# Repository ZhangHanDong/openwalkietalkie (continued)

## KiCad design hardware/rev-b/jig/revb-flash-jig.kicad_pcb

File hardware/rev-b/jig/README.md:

# Rev B UART first-flash jig

This plate flashes a blank Rev B main board over its UART debug pads with no
soldering. The SF32's boot ROM only listens on UART1, so every new board needs
this once, for the flash table and the recovery bootloader. After that, every
update goes over USB-C (`tools/flash-usb.py`). The plate is also the way back
when a bootloader write was interrupted, and it gives you the UART debug log.

| Top (the DUT side) | Bottom |
|---|---|
|  |  |

## How it works

- The DUT lies **battery side (F) down** on the plate. The silkscreen shows its
  outline, which is mirrored because you see the board from its back.
- Three pogo pins touch the debug pads:
  - **TP6** (DUT RX)
  - **TP4** (GND)
  - **TP8** (DUT TX)

  TP3 (CAL), TP5 (reset) and TP10 (3V3) get no pin. Nothing can hold the board
  in reset or feed it through its 3.3 V rail.
- **Locators:** two M2 screws come up through the DUT's own mounting holes
  **MH2 and MH4**, so the board only fits one way.
- **Rests:** four M2×5 standoffs (REST A–D) hold the DUT's F face 5.0 mm above
  the plate.
  - The tallest F-side parts are 3.4 mm (J1/J3 PicoBlade, the USB-C shell), so
    they clear by 1.6 mm.
  - Every rest stands on bare soldermask, at least 3 mm from any F-side part or
    pad and from the board edge.
- **Hold-down:** press on the DUT's back over the pins (no parts there on the B
  side), or put a small binder clip at **CLIP**. That spot is on the DUT edge,
  over REST A.
- **Power:** plug a USB-C cable into the DUT. The plate stops at y = 3 mm, so
  the plug's overmold clears it.
- **J1** is the adapter header:

  | J1 pin | Signal | Wire to the adapter's |
  |---|---|---|
  | 1 | DUT RX | TX |
  | 2 | GND | GND |
  | 3 | DUT TX | RX |

  Any 3.3 V USB-UART adapter works; the DAPLink's CDC UART is the one used so
  far.

Every DUT position (pads, holes, outline) is read from
`../main/main-revb.kicad_pcb` by `scripts/gen_jig.py`. If the main board
moves, regenerate the plate.

## The pogo pin

**Xinyangze YZ105312061P-01, LCSC/JLCPCB C5157237** (extended part, 423 in
stock and about $0.38 on 2026-10-09).

| | |
|---|---|
| Body | 1.24 mm diameter, 0.8 mm plunger, domed tip, gold over brass |
| Length | 6.1 mm overall; operational height 4.2 mm |
| Force | 120 gf rated |
| Life | 10,000 cycles |
| Mount | Reflowed, tail in a 0.70 mm plated hole (self-centring) on a 1.5 mm ring |

Why this part:
- **Width.** TP6 and TP4 are only 2.0 mm apart. Every other pogo pin JLCPCB
  stocks is 2 mm wide (`D=2mm`), and Mill-Max's 0906 (1.07 mm plunger) is out
  of stock at JLCPCB and LCSC.
- **Force.** The 1.2–1.3 mm pins that are in stock (YZ87312060R-01,
  YZP0265-12060-01) are rated 20 gf. That is light for a jig that is pressed by
  hand.

**Check one pin with calipers when it arrives.** The datasheet has no drawing:
- The dimensions above come from the LCSC/EasyEDA 3D model and the listing.
- That model puts the free height at about **5.5 mm above the plate**, so at
  the 5.0 mm rest height the pin compresses about 0.5 mm.
- If contact is weak, use **M2×4.5** standoffs. That gives about 1.0 mm of
  compression and still stops short of the pin's ~1.5 mm stroke.
- Do not shim the standoffs up: higher rests mean less compression.

## Bill of materials

Assembled by JLCPCB (`fab-jlcpcb/`):

| Ref | Part | LCSC | Qty |
|---|---|---|---|
| P1–P3 | Pogo pin, Xinyangze YZ105312061P-01 | C5157237 | 3 |
| J1 | 1×3 2.54 mm pin header, BOOMELE | C49257 | 1 |

Hardware you add:

| Qty | Part | Where |
|---|---|---|
| 4 | M2×5 hex standoff, female–female | REST A–D |
| 4 | M2×4 screw | from below, into the rests |
| 2 | M2×10 screw | LOCATE MH2/MH4, from below |
| 2 | M2 **thin** nut (DIN 439, 1.2 mm) | on top, locks each locator screw |
| 4 | Self-adhesive bumper, about 10 mm diameter, ≥ 5 mm tall | FEET circles on the bottom |

Use the thin nut at MH4: the speaker connector J1 on the DUT hangs to 1.6 mm
above the plate beside it. A standard 1.6 mm nut would touch it. Each
locator screw ends 8.4 mm above the plate, which is 2.4 mm above the DUT's
back.

## Ordering

The JLCPCB package is in `fab-jlcpcb/`:
- `revb-flash-jig-gerber.zip`
- `revb-flash-jig-bom-jlcpcb.csv`
- `revb-flash-jig-cpl-jlcpcb.csv`

Board settings: 2 layers, 62 × 95 mm, 1.6 mm FR4. Any finish works; this is
a tool, not the DUT.

PCBA: top side only.
- The pogo pins are SMT-placed into their plated holes.
- J1 is through-hole (or solder it yourself).
- Check JLCPCB's placement preview: the pins sit 2.0 mm apart.

Order spare pins. They are rated 10k cycles.

## Using it

1. Fit the rests and locators, and stick on the feet.
2. Wire J1 to the adapter: RX→TX, TX→RX, GND.
3. Lay the DUT on the plate battery side down, with the locator screws through
   MH2/MH4. Press it down at CLIP (or clip it), and plug in USB-C.
4. Flash as for Rev A (`tools/flash-uart.py`). The port answers at any time,
   so no power-cycle timing is needed. `--compat true` (the default) covers the
   DAPLink's CDC bridge.
5. From then on, use USB-C only (`tools/flash-usb.py`).

Rev B needs the firmware pin-map changes in
[`../README.md`](../README.md#firmware-changes-needed-before-bring-up) before
its application image is usable. The flash table and bootloader do not depend
on them.

## Files

| What | Where |
|---|---|
| Board (KiCad 10.0.4, generated) | `revb-flash-jig.kicad_pcb`, `.kicad_pro` (the Rev B rules) |
| Pogo footprint + 3D model | `revb-jig.pretty/`, `models/YZ105312061P-01.wrl` (converted from the LCSC/EasyEDA model) |
| Generator | `scripts/gen_jig.py`, run with KiCad's bundled python |
| Fab outputs, DRC, renders | `scripts/make_fab.sh` → `fab-jlcpcb/`, `verification/`, `render-*.png` |
| DRC (all severities) | [`verification/revb-flash-jig-drc.rpt`](verification/revb-flash-jig-drc.rpt): 0 violations, 0 unconnected |

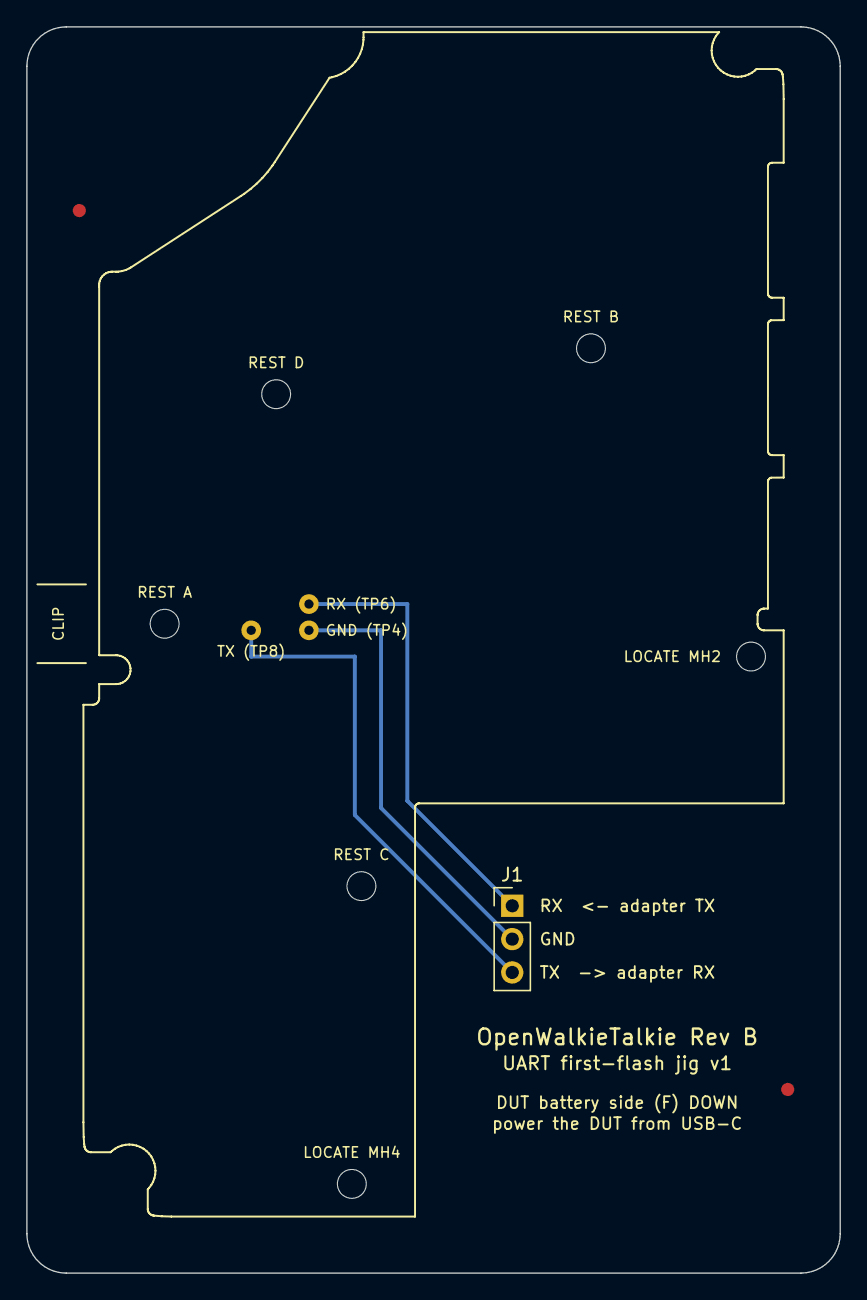
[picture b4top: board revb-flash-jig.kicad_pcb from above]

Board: 2 copper layers, 62.0 x 95.0 mm, 12 parts (0 on the bottom side), 3 nets.

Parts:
FID1, FID2: Fiducial; Fiducial_1mm_Mask2mm
H1: LOCATE MH2; MountingHole_2.2mm_M2
H2: LOCATE MH4; MountingHole_2.2mm_M2
H3: REST A; MountingHole_2.2mm_M2
H4: REST B; MountingHole_2.2mm_M2
H5: REST D; MountingHole_2.2mm_M2
H6: REST C; MountingHole_2.2mm_M2
J1: UART; PinHeader_1x03_P2.54mm_Vertical
P1, P2, P3: YZ105312061P-01; Pogo_Xinyangze_YZ105312061P-01

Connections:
DUT_RX: J1.1, P1.1
DUT_TX: J1.3, P3.1
GND: J1.2, P2.1

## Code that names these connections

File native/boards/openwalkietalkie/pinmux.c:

/*
 * SPDX-FileCopyrightText: 2019-2022 SiFli Technologies(Nanjing) Co., Ltd
 *
 * SPDX-License-Identifier: Apache-2.0
 */

#include "bsp_board.h"

#ifdef BSP_USING_PSRAM1
/* APS 128p*/
static void board_pinmux_psram_func0()
{
    HAL_PIN_Set(PAD_SA01, MPI1_DIO0, PIN_PULLDOWN, 1);
    HAL_PIN_Set(PAD_SA02, MPI1_DIO1, PIN_PULLDOWN, 1);
    HAL_PIN_Set(PAD_SA03, MPI1_DIO2, PIN_PULLDOWN, 1);
    HAL_PIN_Set(PAD_SA04, MPI1_DIO3, PIN_PULLDOWN, 1);
    HAL_PIN_Set(PAD_SA05, MPI1_DIO4, PIN_PULLDOWN, 1);
    HAL_PIN_Set(PAD_SA06, MPI1_DIO5, PIN_PULLDOWN, 1);
    HAL_PIN_Set(PAD_SA07, MPI1_DIO6, PIN_PULLDOWN, 1);
    HAL_PIN_Set(PAD_SA08, MPI1_DIO7, PIN_PULLDOWN, 1);
    HAL_PIN_Set(PAD_SA09, MPI1_DQSDM, PIN_PULLDOWN, 1);
    HAL_PIN_Set(PAD_SA10, MPI1_CLK,  PIN_NOPULL, 1);
    HAL_PIN_Set(PAD_SA11, MPI1_CS,   PIN_NOPULL, 1);

    HAL_PIN_Set_Analog(PAD_SA00, 1);
    HAL_PIN_Set_Analog(PAD_SA12, 1);
}

/* APS 1:64p 2:32P, 4:Winbond 32/64/128p*/
static void board_pinmux_psram_func1_2_4(int func)
{
    HAL_PIN_Set(PAD_SA01, MPI1_DIO0, PIN_PULLDOWN, 1);
    HAL_PIN_Set(PAD_SA02, MPI1_DIO1, PIN_PULLDOWN, 1);
    HAL_PIN_Set(PAD_SA03, MPI1_DIO2, PIN_PULLDOWN, 1);
    HAL_PIN_Set(PAD_SA04, MPI1_DIO3, PIN_PULLDOWN, 1);
    HAL_PIN_Set(PAD_SA08, MPI1_DIO4, PIN_PULLDOWN, 1);
    HAL_PIN_Set(PAD_SA09, MPI1_DIO5, PIN_PULLDOWN, 1);
    HAL_PIN_Set(PAD_SA10, MPI1_DIO6, PIN_PULLDOWN, 1);
    HAL_PIN_Set(PAD_SA11, MPI1_DIO7, PIN_PULLDOWN, 1);
    HAL_PIN_Set(PAD_SA07, MPI1_CLK,  PIN_NOPULL, 1);
    HAL_PIN_Set(PAD_SA05, MPI1_CS,   PIN_NOPULL, 1);

#ifdef FPGA
    HAL_PIN_Set(PAD_SA00, MPI1_DM, PIN_PULLDOWN, 1);
    HAL_PIN_Set(PAD_SA06, MPI1_CLKB, PIN_NOPULL, 1);
    HAL_PIN_Set(PAD_SA12, MPI1_DQSDM, PIN_PULLDOWN, 1);
#else
    switch (func)
    {
    case 1:             // APS 64P XCELLA
        HAL_PIN_Set(PAD_SA12, MPI1_DQSDM, PIN_PULLDOWN, 1);
        HAL_PIN_Set_Analog(PAD_SA00, 1);
        HAL_PIN_Set_Analog(PAD_SA06, 1);
        break;
    case 2:             // APS 32P LEGACY
        HAL_PIN_Set(PAD_SA00, MPI1_DM, PIN_PULLDOWN, 1);
        HAL_PIN_Set(PAD_SA12, MPI1_DQS, PIN_PULLDOWN, 1);
        HAL_PIN_Set(PAD_SA06, MPI1_CLKB, PIN_NOPULL, 1);
        break;
    case 4:             // Winbond 32/64/128p
        //HAL_PIN_Set(PAD_SA06, MPI1_CLKB, PIN_NOPULL, 1);
        HAL_PIN_Set(PAD_SA12, MPI1_DQSDM, PIN_NOPULL, 1);
        HAL_PIN_Set_Analog(PAD_SA00, 1);
        HAL_PIN_Set_Analog(PAD_SA06, 1);
        break;
    }
#endif
}

/* APS 16p*/
static void board_pinmux_psram_func3()
{
    HAL_PIN_Set(PAD_SA09, MPI1_CLK, PIN_NOPULL, 1);
    HAL_PIN_Set(PAD_SA08, MPI1_CS,  PIN_NOPULL, 1);
    HAL_PIN_Set(PAD_SA05, MPI1_DIO0, PIN_PULLDOWN, 1);
    HAL_PIN_Set(PAD_SA07, MPI1_DIO1, PIN_PULLDOWN, 1);
    HAL_PIN_Set(PAD_SA06, MPI1_DIO2, PIN_PULLUP, 1);
    HAL_PIN_Set(PAD_SA10, MPI1_DIO3, PIN_PULLUP, 1);

    HAL_PIN_Set_Analog(PAD_SA00, 1);
    HAL_PIN_Set_Analog(PAD_SA01, 1);
    HAL_PIN_Set_Analog(PAD_SA02, 1);
    HAL_PIN_Set_Analog(PAD_SA03, 1);
    HAL_PIN_Set_Analog(PAD_SA04, 1);
    HAL_PIN_Set_Analog(PAD_SA11, 1);
    HAL_PIN_Set_Analog(PAD_SA12, 1);
}

static void board_pinmux_mpi1_none(void)
{
    uint32_t i;

    for (i = 0; i <= 12; i++)
    {
        HAL_PIN_Set_Analog(PAD_SA00 + i, 1);
    }
}
#endif

void BSP_PIN_Init(void)
{
#ifdef SOC_BF0_HCPU
#ifdef BSP_USING_PSRAM1
    unsigned pid = (hwp_hpsys_cfg->IDR & HPSYS_CFG_IDR_PID_Msk) >> HPSYS_CFG_IDR_PID_Pos;
    switch (pid & 7) {
    case 5: board_pinmux_psram_func3(); break;
    case 4: board_pinmux_psram_func1_2_4(2); break;
    case 6: board_pinmux_psram_func1_2_4(4); break;
    case 3: board_pinmux_psram_func1_2_4(1); break;
    case 2: board_pinmux_psram_func0(); break;
    default: board_pinmux_mpi1_none(); break;
    }
#endif
    HAL_PIN_Set(PAD_PA16, MPI2_CLK, PIN_NOPULL, 1);
    HAL_PIN_Set(PAD_PA12, MPI2_CS, PIN_NOPULL, 1);
    HAL_PIN_Set(PAD_PA15, MPI2_DIO0, PIN_PULLDOWN, 1);
    HAL_PIN_Set(PAD_PA13, MPI2_DIO1, PIN_PULLDOWN, 1);
    HAL_PIN_Set(PAD_PA14, MPI2_DIO2, PIN_PULLUP, 1);
    HAL_PIN_Set(PAD_PA17, MPI2_DIO3, PIN_PULLUP, 1);
    HAL_PIN_Set(PAD_PA18, USART1_RXD, PIN_PULLUP, 1);
    HAL_PIN_Set(PAD_PA19, USART1_TXD, PIN_PULLUP, 1);
    HAL_PIN_Set(PAD_PA20, GPIO_A20, PIN_PULLDOWN, 1); /* NS4150B speaker enable (Rev A; unconnected on Rev B) */
#ifdef OWT_BOARD_HW_A
    /* OpenWalkieTalkie Rev A (BodyV6.13 r6): the net list is
     * hardware/rev-a/pcb-release-bodyv6.13-20260923-r6/source/main/src/main.cohdl.
     * The board carries every pull-up the inputs need (100k; I2C 10k). */
#ifdef OWT_BOARD_HW_B
    /* Rev B (hardware/rev-b/main/main-revb.kicad_pcb): the same map with three
     * pins moved. The amplifier enable is on PA01, the CAL test pad TP3 on
     * PA00 (parked), and the BQ24073's CHG output reaches PA33 (R46 100k
     * pull-up on the board; low while charging). */
    HAL_PIN_Set(PAD_PA01, GPIO_A1, PIN_PULLDOWN, 1);  /* AMP_ENABLE: NS4150B CTRL, off until driven */
    HAL_PIN_Set(PAD_PA00, GPIO_A0, PIN_PULLDOWN, 1);  /* CAL (TP3) */
    HAL_PIN_Set(PAD_PA33, GPIO_A33, PIN_NOPULL, 1);   /* CHG_STATUS */
#endif
    /* Both enables have 1M pull-downs on the board (R34, R36); no internal pull
     * to fight the high level BSP_Power_Up drives for the whole runtime. */
    HAL_PIN_Set(PAD_PA10, GPIO_A10, PIN_NOPULL, 1);   /* PANEL_ENABLE: U8 PANEL_4V */
    HAL_PIN_Set(PAD_PA11, GPIO_A11, PIN_NOPULL, 1);   /* PANEL_VCI_ENABLE: U10 PANEL_LOGIC */
    HAL_PIN_Set(PAD_PA09, GPIO_A9, PIN_NOPULL, 1);    /* PANEL_RESET, 100k pull-down on the board */
    HAL_PIN_Set(PAD_PA44, GPIO_A44, PIN_NOPULL, 1);   /* TOUCH_RESET */
    HAL_PIN_Set(PAD_PA43, GPIO_A43, PIN_NOPULL, 1);   /* TOUCH_IRQ */
    HAL_PIN_Set(PAD_PA42, I2C1_SCL, PIN_NOPULL, 1);
    HAL_PIN_Set(PAD_PA41, I2C1_SDA, PIN_NOPULL, 1);
    HAL_PIN_Set(PAD_PA24, GPIO_A24, PIN_NOPULL, 1);   /* PTT */
    HAL_PIN_Set(PAD_PA25, GPIO_A25, PIN_NOPULL, 1);   /* ENTER */
    HAL_PIN_Set(PAD_PA26, GPIO_A26, PIN_NOPULL, 1);   /* ESC */
    HAL_PIN_Set(PAD_PA27, GPIO_A27, PIN_NOPULL, 1);   /* SHIFT */
    HAL_PIN_Set(PAD_PA37, GPIO_A37, PIN_NOPULL, 1);   /* MACRO_LEFT */
    HAL_PIN_Set(PAD_PA38, GPIO_A38, PIN_NOPULL, 1);   /* MACRO_RIGHT */
    HAL_PIN_Set(PAD_PA39, GPIO_A39, PIN_NOPULL, 1);   /* ENC_A */
    HAL_PIN_Set(PAD_PA40, GPIO_A40, PIN_NOPULL, 1);   /* ENC_B */
    HAL_PIN_Set(PAD_PA28, GPIO_A28, PIN_PULLDOWN, 1); /* MIC_POWER_ENABLE: load switch for the MP34DT05, driven by board.c while the PDM block runs */
    /* PDM1 to the MP34DT05 (L/R tied low: left channel). PA22 doubles as
     * XTAL32K_XI, which this board does not fit (LXT_DISABLE). */
    HAL_PIN_Set(PAD_PA22, PDM1_CLK, PIN_NOPULL, 1);   /* MIC_PDM_CLK through 22 ohm */
    HAL_PIN_Set(PAD_PA23, PDM1_DATA, PIN_PULLDOWN, 1); /* MIC_PDM_DATA, 100k pull-down on the board too */
#else
    HAL_PIN_Set(PAD_PA41, GPIO_A41, PIN_PULLUP, 1);
    HAL_PIN_Set(PAD_PA44, GPIO_A44, PIN_PULLUP, 1);
    HAL_PIN_Set(PAD_PA09, GPIO_A9, PIN_PULLUP, 1);
    HAL_PIN_Set(PAD_PA00, GPIO_A0, PIN_NOPULL, 1);
    HAL_PIN_Set(PAD_PA01, GPIO_A1, PIN_PULLUP, 1);
    HAL_PIN_Set(PAD_PA11, GPIO_A11, PIN_PULLUP, 1);
    HAL_PIN_Set(PAD_PA38, I2C1_SCL, PIN_PULLUP, 1);
    HAL_PIN_Set(PAD_PA37, I2C1_SDA, PIN_PULLUP, 1);
#endif
    HAL_PIN_Set(PAD_PA02, LCDC1_SPI_TE, PIN_NOPULL, 1);
    HAL_PIN_Set(PAD_PA03, LCDC1_SPI_CS, PIN_NOPULL, 1);
    HAL_PIN_Set(PAD_PA04, LCDC1_SPI_CLK, PIN_NOPULL, 1);
    HAL_PIN_Set(PAD_PA05, LCDC1_SPI_DIO0, PIN_NOPULL, 1);
    HAL_PIN_Set(PAD_PA06, LCDC1_SPI_DIO1, PIN_NOPULL, 1);
    HAL_PIN_Set(PAD_PA07, LCDC1_SPI_DIO2, PIN_NOPULL, 1);
    HAL_PIN_Set(PAD_PA08, LCDC1_SPI_DIO3, PIN_NOPULL, 1);
#endif
}

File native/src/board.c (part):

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 * sets from OWT_BOARD=hw-a / hw-b. */
#ifdef OWT_BOARD_HW_A
#ifdef OWT_BOARD_HW_B
#define OWT_CHG_PIN 33 /* BQ24073 CHG, open drain with R46 100k to IO_3V3: low while charging */
#endif
#define OWT_TOUCH_IRQ_PIN 43
#define OWT_TOUCH_RESET_PIN 44
#define OWT_PANEL_POWER_PIN 10  /* PANEL_ENABLE: U8 makes PANEL_4V */
#define OWT_PANEL_LOGIC_PIN 11  /* PANEL_VCI_ENABLE: U10 switches PANEL_LOGIC */
#define OWT_SYSTEM_EN_PIN OWT_PANEL_LOGIC_PIN /* stands in for the dev board's 3V3_EN in diagnostics */
#define OWT_DIAG_SECOND_PIN 39  /* encoder A stands in for the keypad IRQ slot */
#define OWT_SECOND_IRQ_NAME "input_irq"
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#endif

#ifdef OWT_BOARD_HW_A
#define OWT_MIC_POWER_PIN 28 /* MIC_POWER_ENABLE: the load switch feeding the MP34DT05's 3.3 V */
void BSP_GPIO_Set(int pin, int value, int is_porta);
HAL_StatusTypeDef __real_HAL_PDM_Init(PDM_HandleTypeDef *hpdm);
HAL_StatusTypeDef __real_HAL_PDM_DeInit(PDM_HandleTypeDef *hpdm);
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    display_pixels = display_transfer_ms = 0;
    rt_hw_interrupt_enable(level);
    rt_kprintf("display: pixels=%u dma_ms=%u\n", pixels, dma_ms);
    rt_kprintf("input: touch_irq=%u " OWT_SECOND_IRQ_NAME "=%u touch_reads=%u touch_errors=%u keypad_errors=%u pins=%u/%02x battery_mv=%u uptime_ms=%u\n",
               touch_edges, key_edges, touch_reads, touch_errors, keypad_errors,
               rt_pin_read(OWT_TOUCH_IRQ_PIN), input_word(), battery_mv, now);
    touch_reads = touch_errors = keypad_errors = 0;
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{
    /* Cold initialization is also used after panel-only reset on wake.
     * Restore the interface and brightness registers instead of relying on
     * their retention through a long panel sleep. Touch PA0 is untouched. */
    static const uint8_t init[][2] = {
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    rt_thread_mdelay(3);
    rt_pin_write(OWT_TOUCH_RESET_PIN, PIN_HIGH);
    rt_thread_mdelay(50);
    rt_err_t touch_irq = rt_pin_attach_irq(OWT_TOUCH_IRQ_PIN, PIN_IRQ_MODE_FALLING, touch_interrupt, RT_NULL);
    if (touch_irq == RT_EOK) touch_irq = rt_pin_irq_enable(OWT_TOUCH_IRQ_PIN, PIN_IRQ_ENABLE);
#ifdef OWT_BOARD_HW_A
    unsigned input_irqs_ok = 0;
    for (unsigned i = 0; i < 8; i++) {
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        if (irq == RT_EOK) irq = rt_pin_irq_enable(input_pins[i], PIN_IRQ_ENABLE);
        input_irqs_ok += irq == RT_EOK;
    }
    rt_kprintf("input: touch IRQ=%u (PA%u), %u/8 direct input IRQs (PTT PA24 ENTER PA25 ESC PA26 SHIFT PA27 LEFT PA37 RIGHT PA38 wheel PA39/PA40), levels=%02x, idle fallback=50ms\n",
               touch_irq == RT_EOK, OWT_TOUCH_IRQ_PIN, input_irqs_ok, owt_inputs_read());
#ifdef OWT_BOARD_HW_B
    rt_pin_mode(OWT_CHG_PIN, PIN_MODE_INPUT);
    rt_kprintf("charger: BQ24073 CHG on PA%u reads %s\n", OWT_CHG_PIN,
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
